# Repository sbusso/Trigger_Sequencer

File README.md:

# Trigger_Sequencer
4 channel 8 step trigger Eurorack sequencer with independent lenght and clock using an Arduino Nano.

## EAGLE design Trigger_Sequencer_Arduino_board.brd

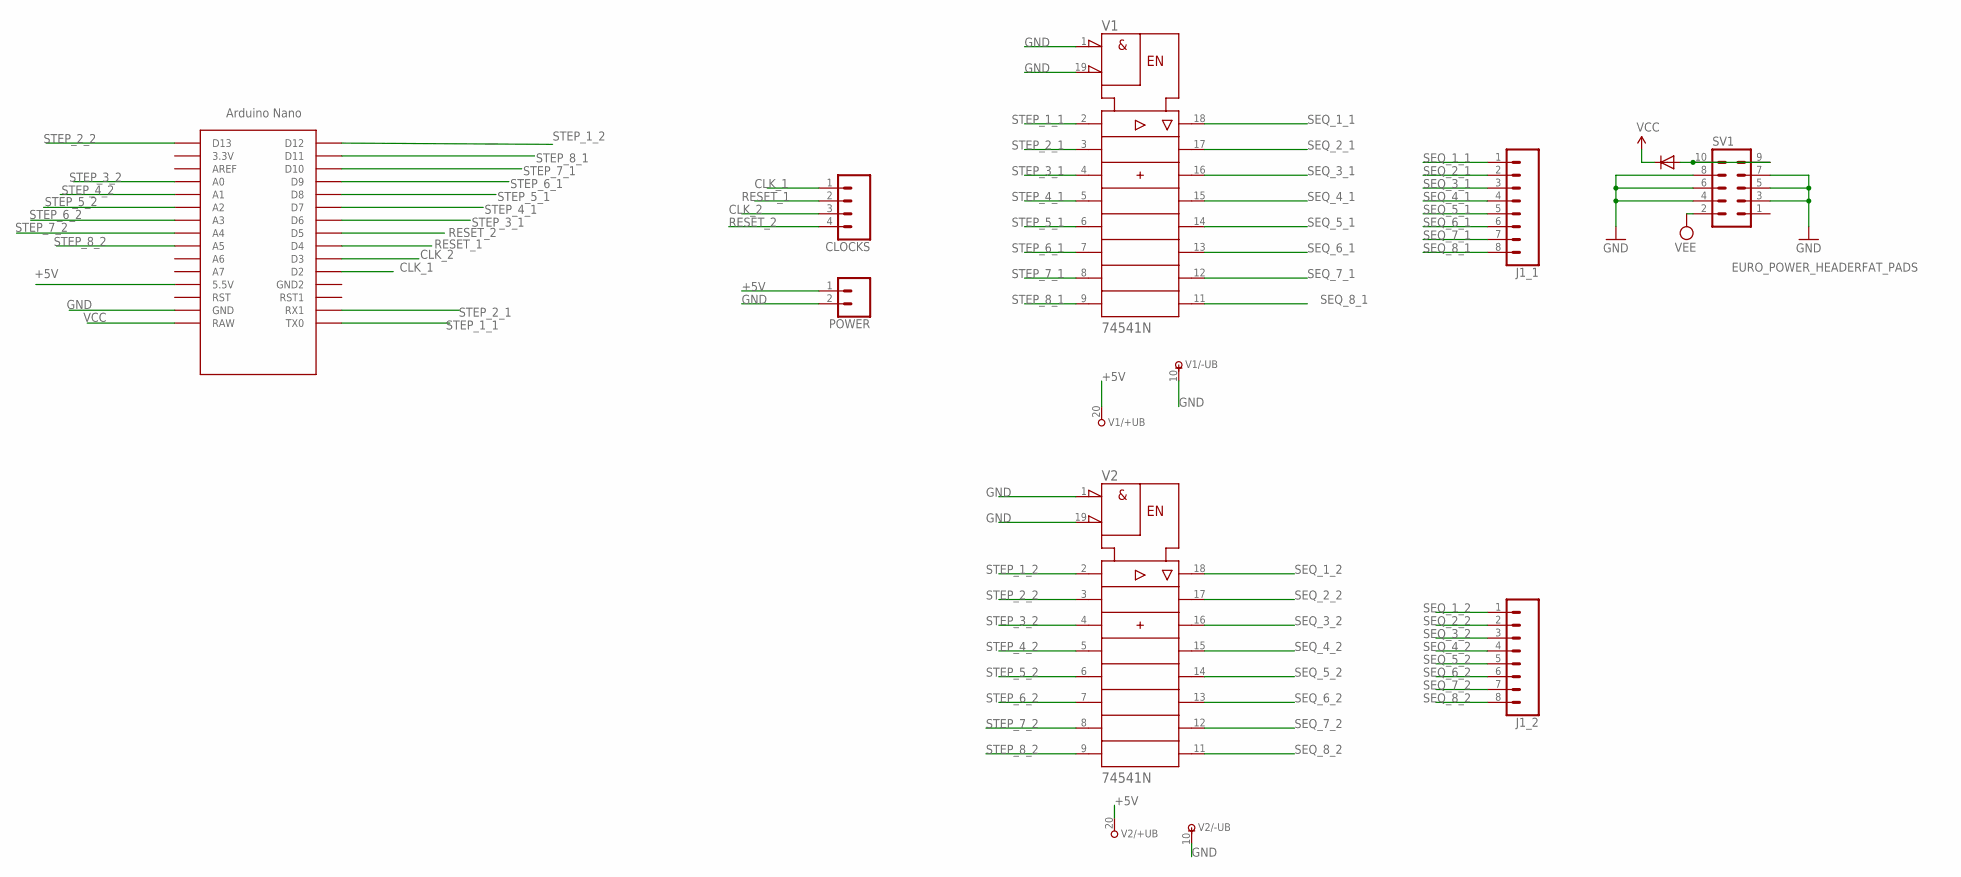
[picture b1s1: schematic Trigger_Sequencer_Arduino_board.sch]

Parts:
CLOCKS: CONN_04; 1X04
D2: 1N5819HW; DO-1N4148
J1_1, J1_2: CONN_08NO_SILK_FEMALE_PTH; 1X08_NO_SILK
POWER: CONN_02; 1X02
SV1: EURO_POWER_HEADERFAT_PADS; EURO_PWR_HEADER_FAT
U$1: NANO
V1, V2: 74541N; DIL20

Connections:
+5V: POWER.1, U$1.5V (5.5V), V1.20 (+UB), V2.20 (+UB)
CLK_1: CLOCKS.1, U$1.D2
CLK_2: CLOCKS.3, U$1.D3
GND: POWER.2, SV1.3, SV1.4, SV1.5, SV1.6, SV1.7, SV1.8, U$1.GND, V1.1 (!G1), V1.10 (-UB), V1.19 (!G2), V2.1 (!G1), V2.10 (-UB), V2.19 (!G2)
unnamed: D2.A, SV1.9, SV1.10
RESET_1: CLOCKS.2, U$1.D4
RESET_2: CLOCKS.4, U$1.D5
SEQ_1_1: J1_1.1, V1.18 (Y1)
SEQ_1_2: J1_2.1, V2.18 (Y1)
SEQ_2_1: J1_1.2, V1.17 (Y2)
SEQ_2_2: J1_2.2, V2.17 (Y2)
SEQ_3_1: J1_1.3, V1.16 (Y3)
SEQ_3_2: J1_2.3, V2.16 (Y3)
SEQ_4_1: J1_1.4, V1.15 (Y4)
SEQ_4_2: J1_2.4, V2.15 (Y4)
SEQ_5_1: J1_1.5, V1.14 (Y5)
SEQ_5_2: J1_2.5, V2.14 (Y5)
SEQ_6_1: J1_1.6, V1.13 (Y6)
SEQ_6_2: J1_2.6, V2.13 (Y6)
SEQ_7_1: J1_1.7, V1.12 (Y7)
SEQ_7_2: J1_2.7, V2.12 (Y7)
SEQ_8_1: J1_1.8, V1.11 (Y8)
SEQ_8_2: J1_2.8, V2.11 (Y8)
STEP_1_1: U$1.TX0, V1.2 (A1)
STEP_1_2: U$1.D12, V2.2 (A1)
STEP_2_1: U$1.RX1, V1.3 (A2)
STEP_2_2: U$1.D13, V2.3 (A2)
STEP_3_1: U$1.D6, V1.4 (A3)
STEP_3_2: U$1.A0, V2.4 (A3)
STEP_4_1: U$1.D7, V1.5 (A4)
STEP_4_2: U$1.A1, V2.5 (A4)
STEP_5_1: U$1.D8, V1.6 (A5)
STEP_5_2: U$1.A2, V2.6 (A5)
STEP_6_1: U$1.D9, V1.7 (A6)
STEP_6_2: U$1.A3, V2.7 (A6)
STEP_7_1: U$1.D10, V1.8 (A7)
STEP_7_2: U$1.A4, V2.8 (A7)
STEP_8_1: U$1.D11, V1.9 (A8)
STEP_8_2: U$1.A5, V2.9 (A8)
VCC: D2.C, U$1.RAW
VEE: SV1.2

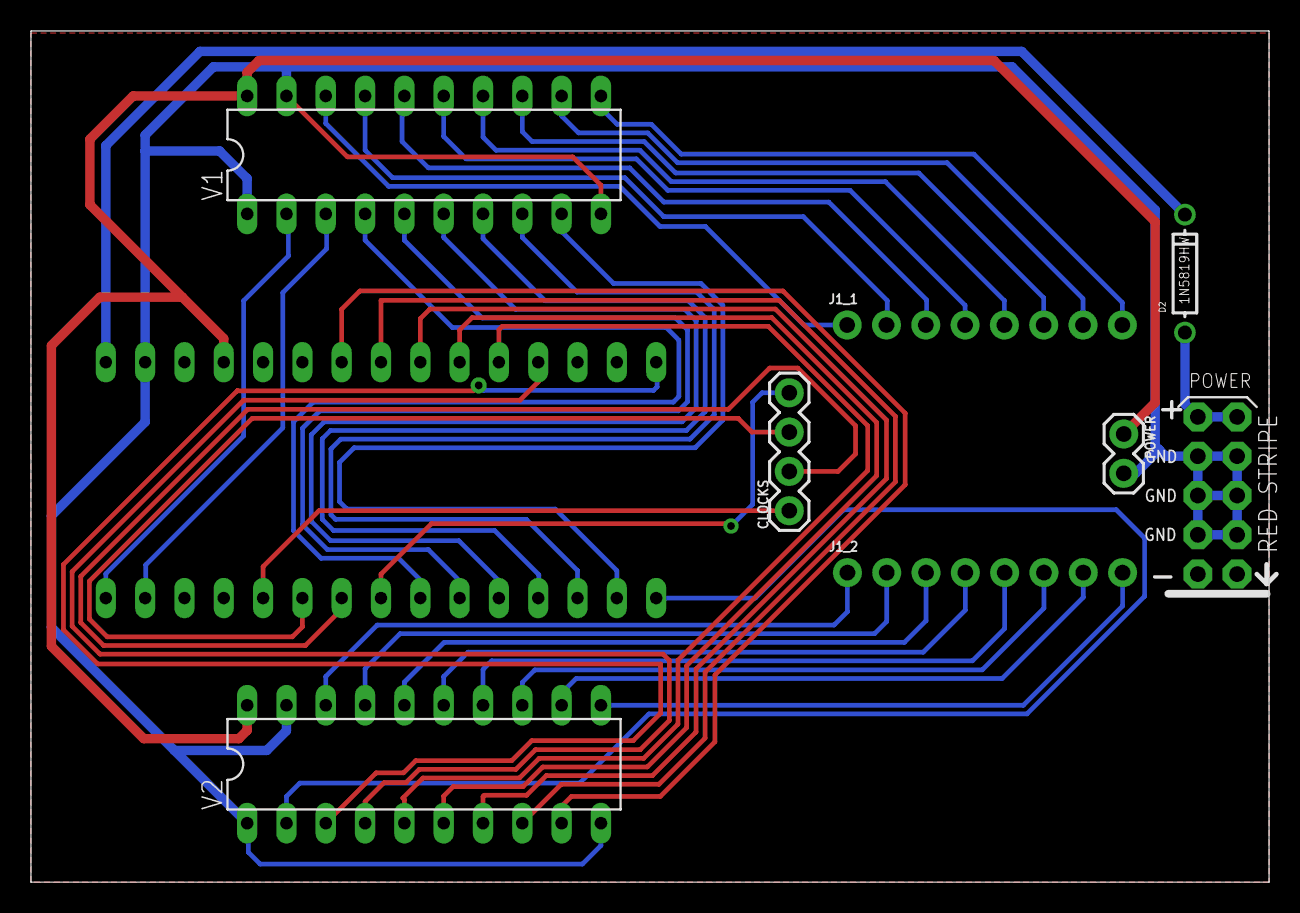
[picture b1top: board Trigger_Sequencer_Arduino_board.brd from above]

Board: 2 copper layers, 80.0 x 55.0 mm, 9 parts (0 on the bottom side), 40 nets.

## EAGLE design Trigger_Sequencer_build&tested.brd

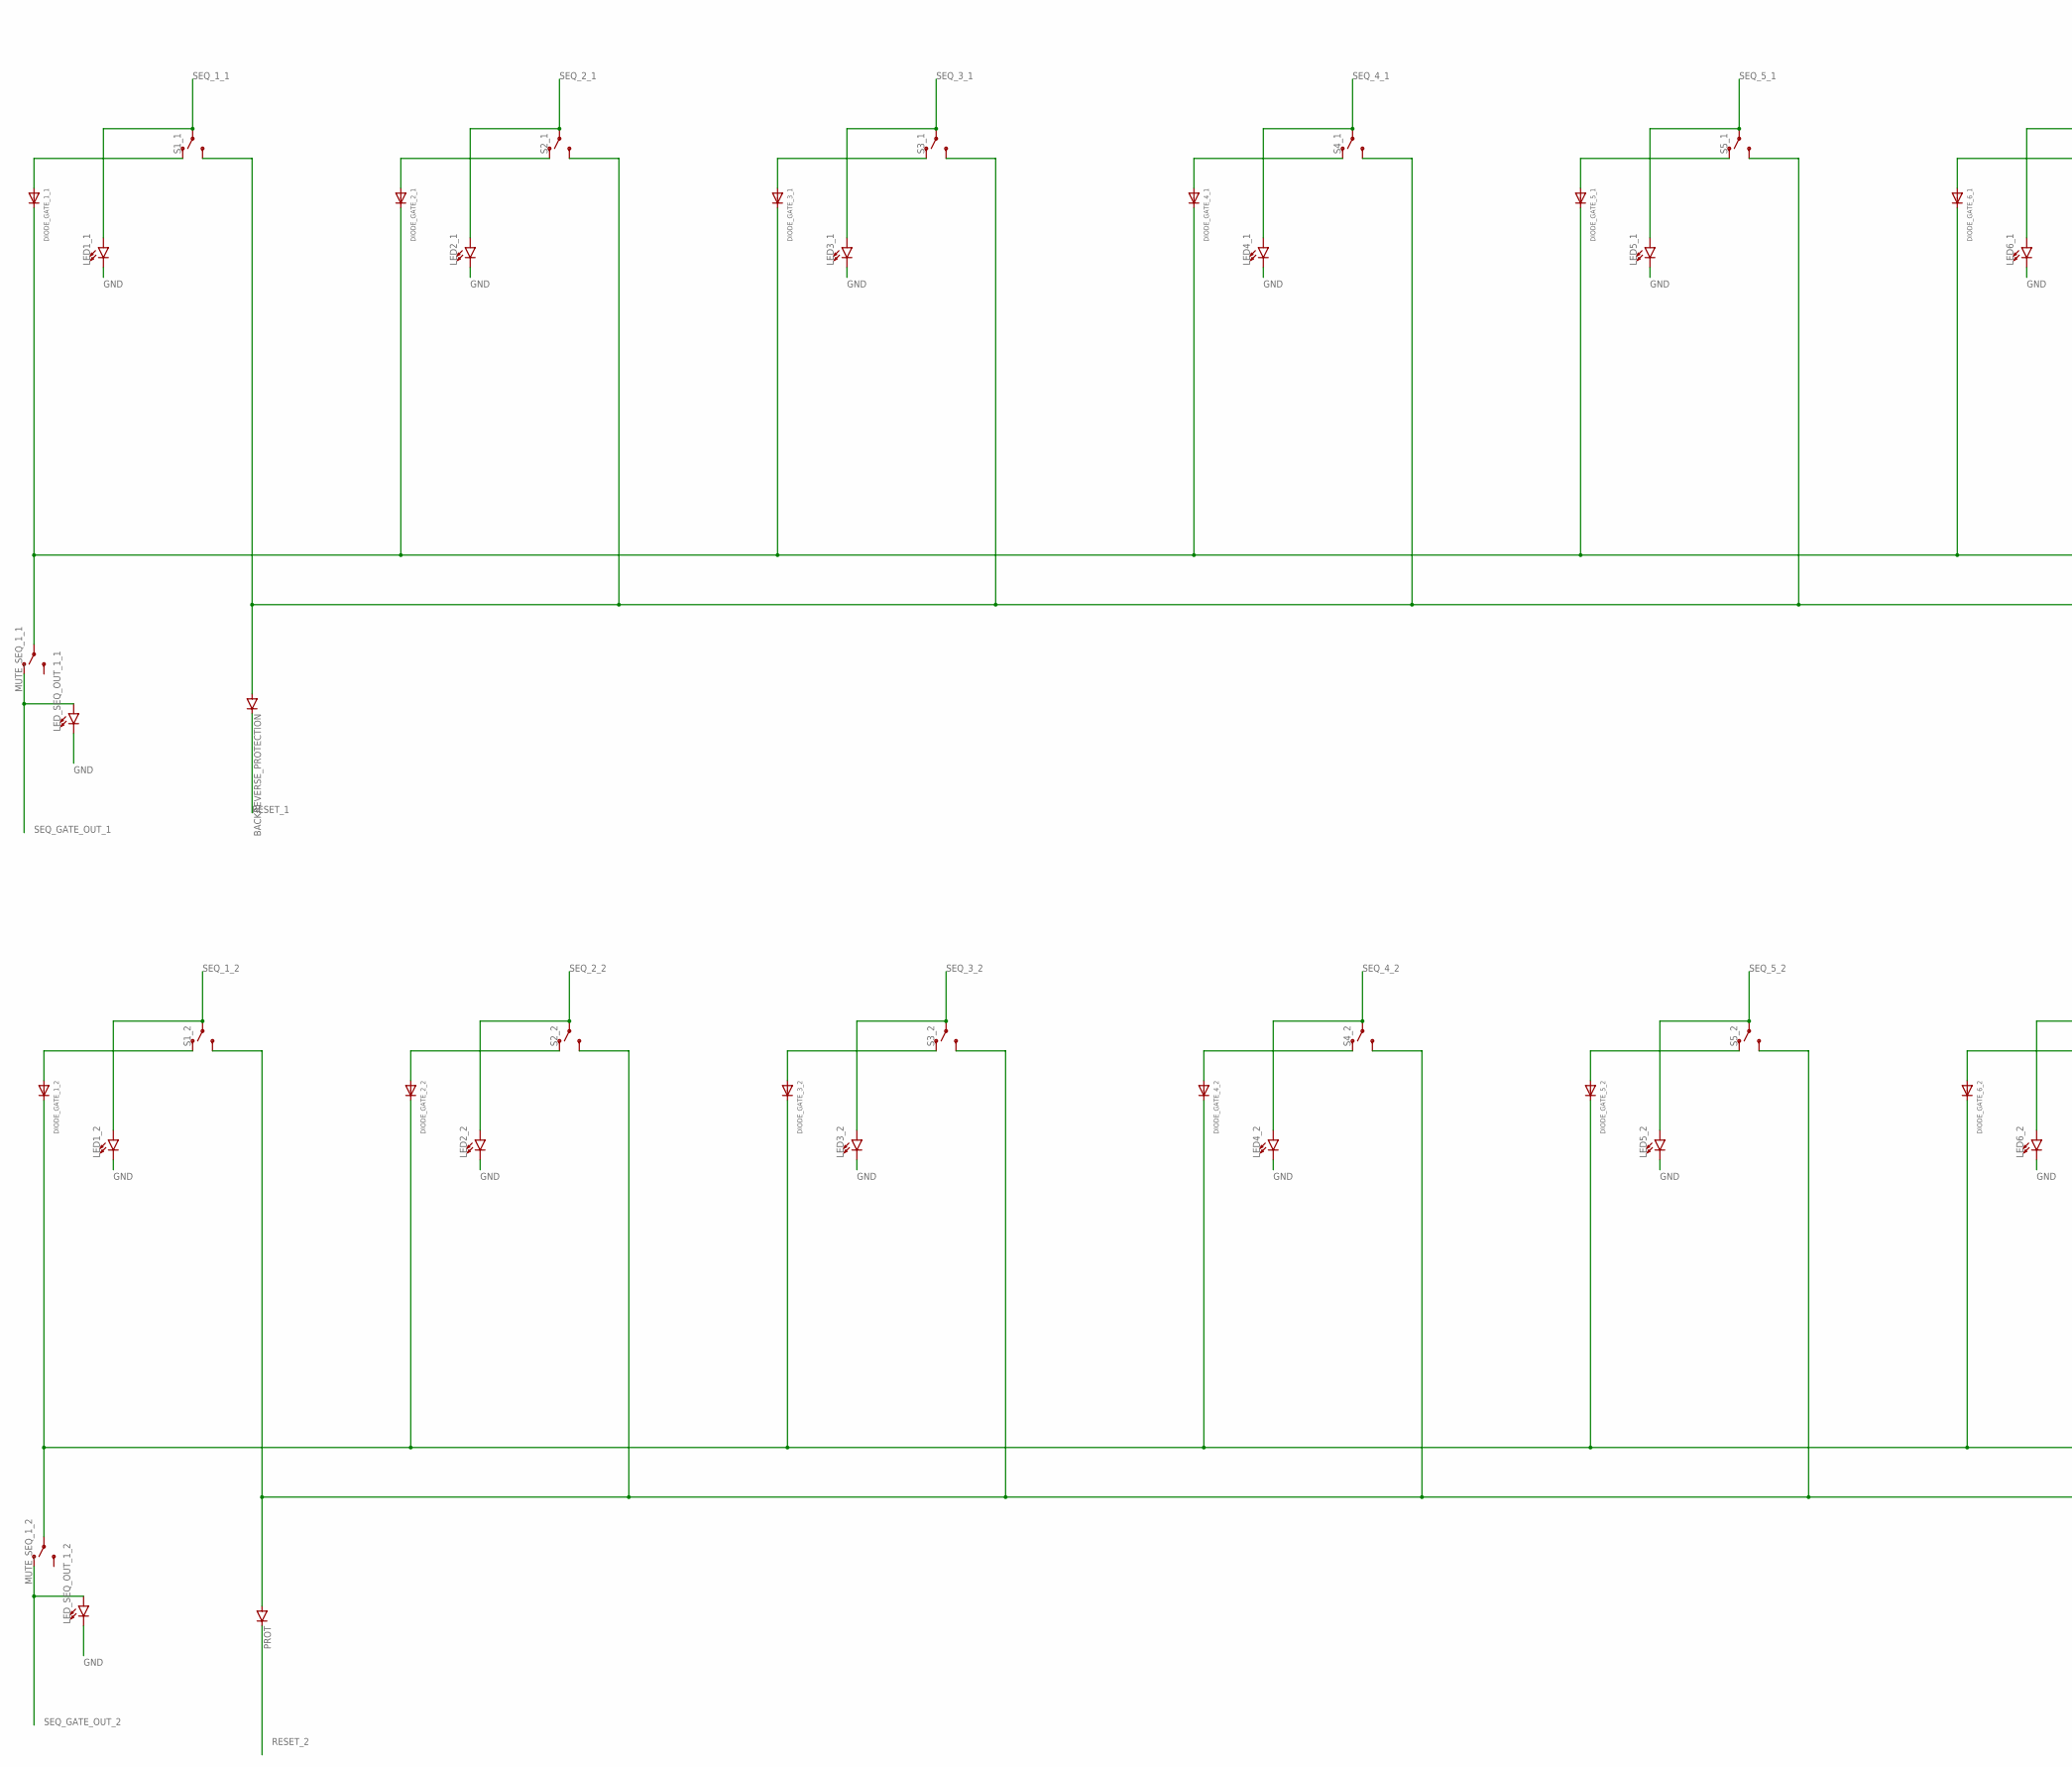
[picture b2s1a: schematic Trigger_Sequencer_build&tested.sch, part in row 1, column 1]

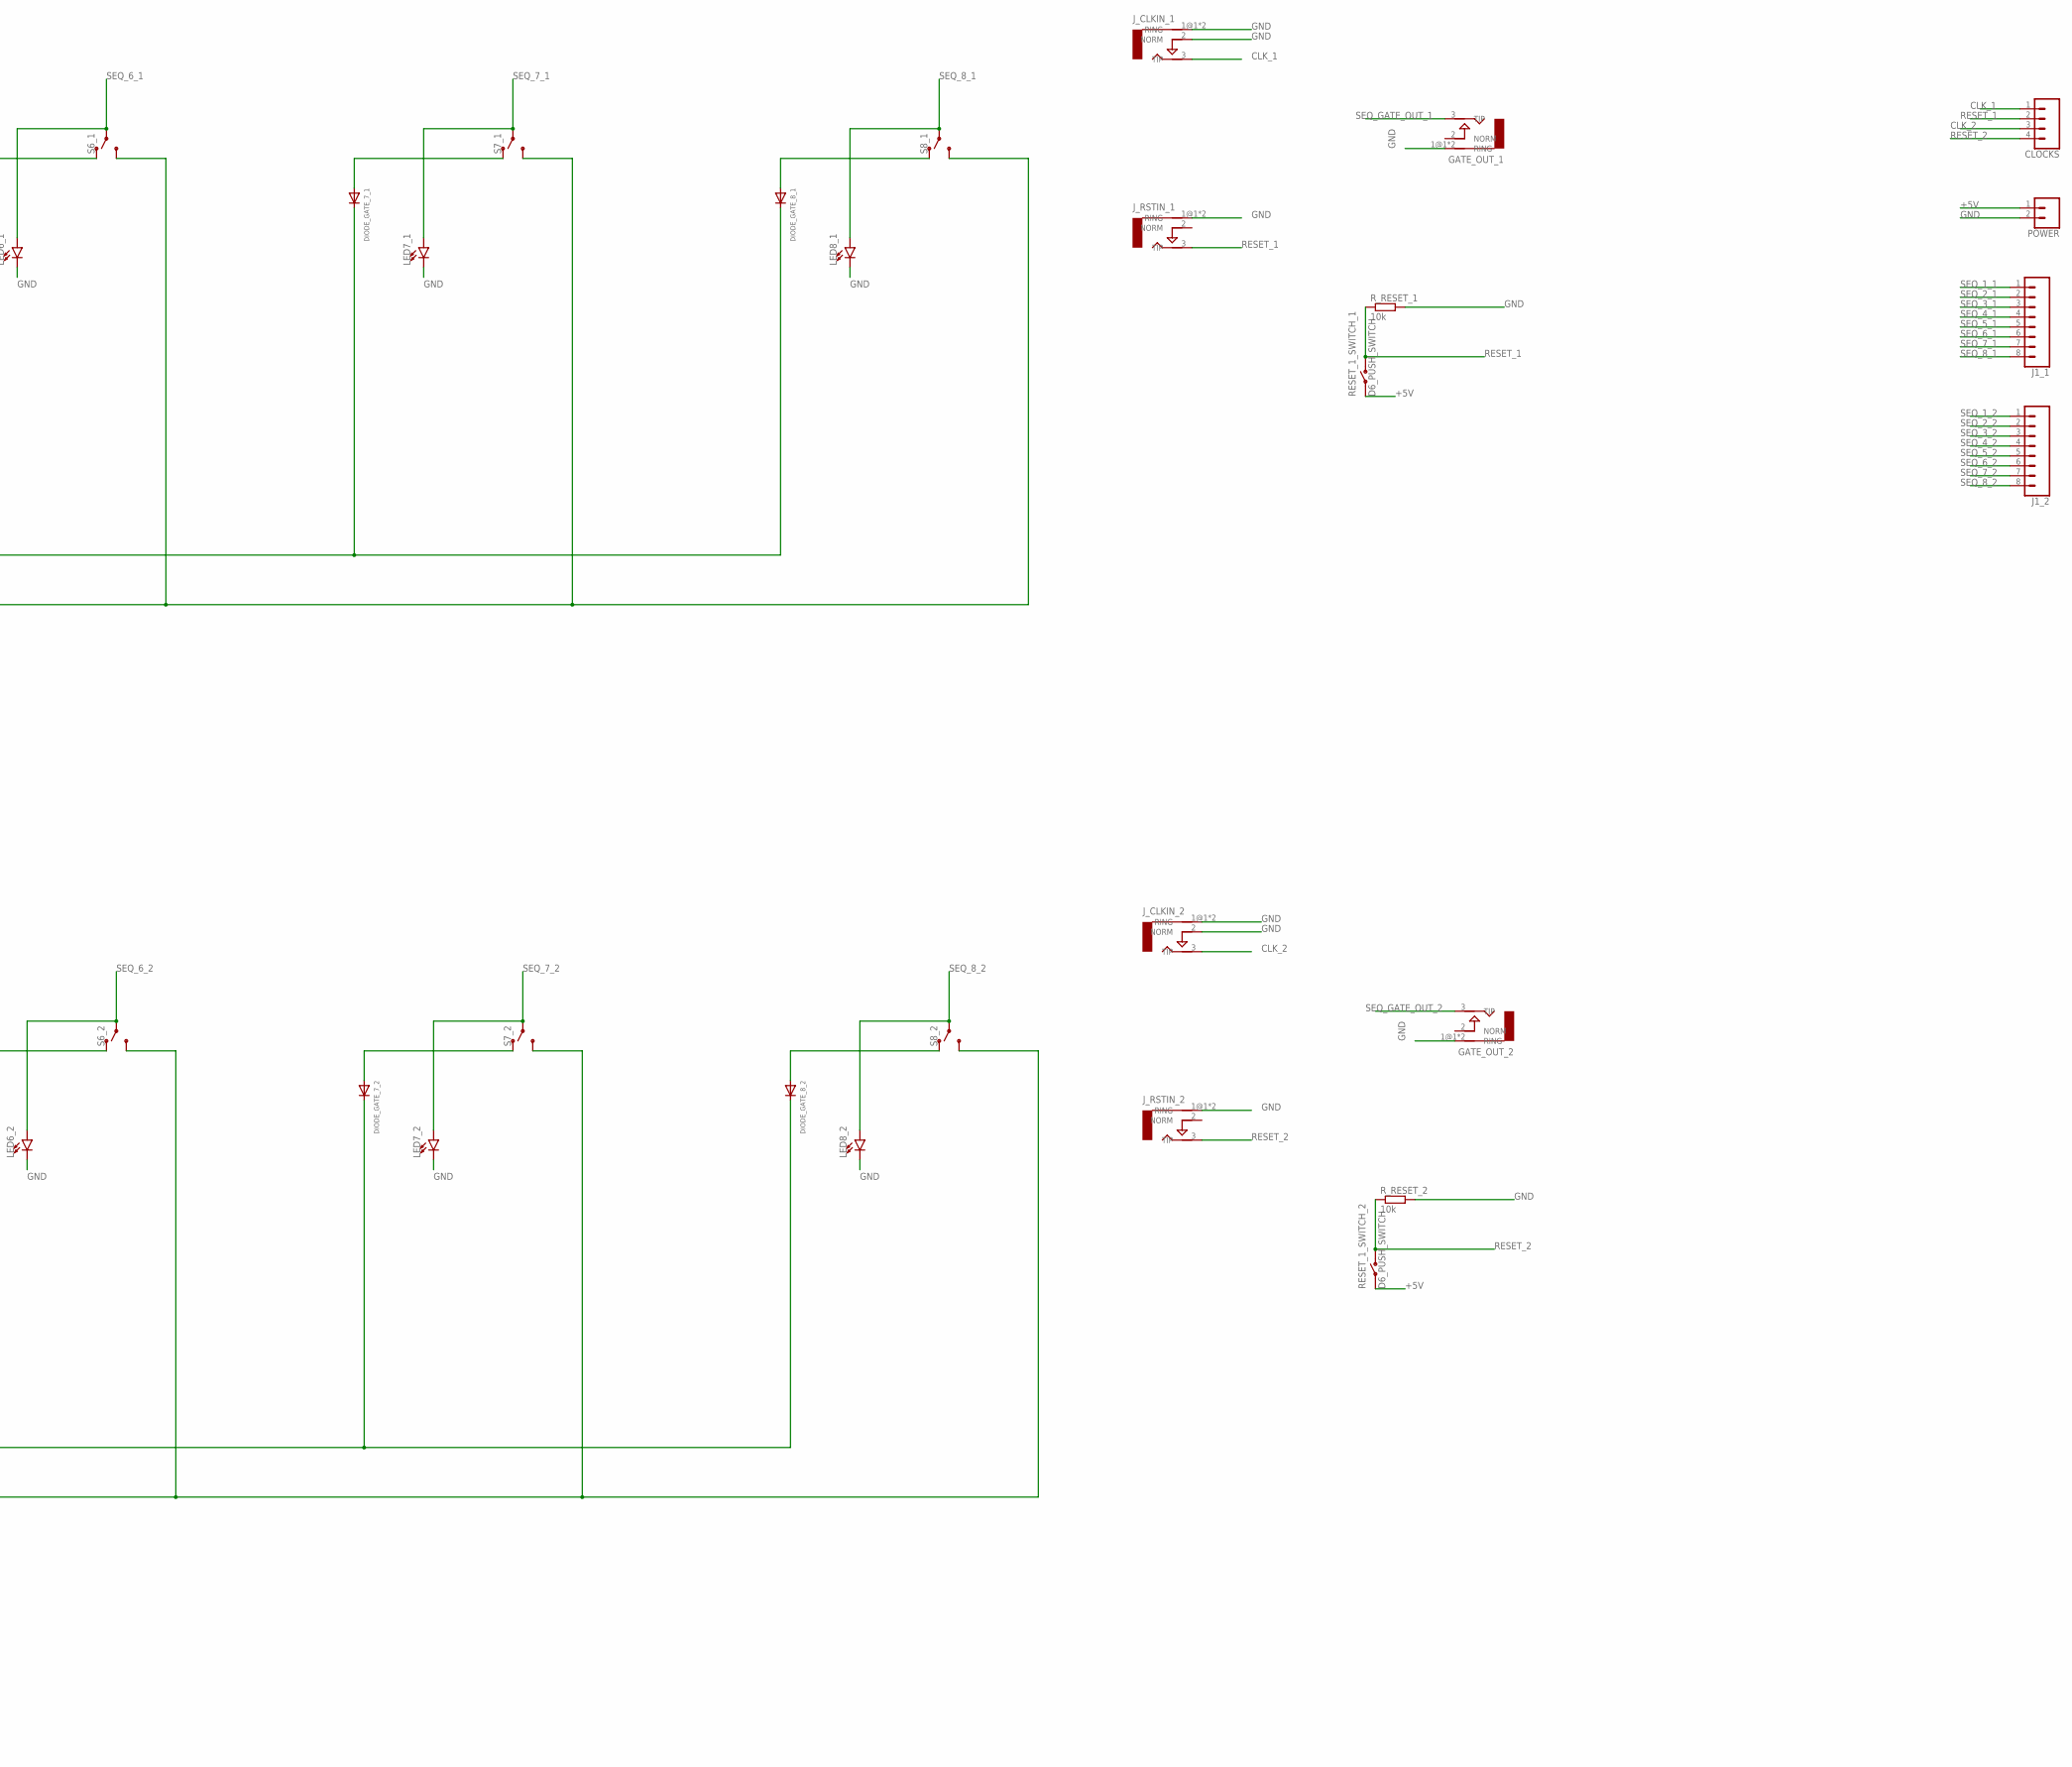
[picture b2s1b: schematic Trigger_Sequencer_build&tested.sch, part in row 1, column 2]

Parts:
BACKREVERSE_PROTECTION: DIODE1N4148; DIODE-1N4148
CLOCKS: CONN_04; 1X04
DIODE_GATE_1_1, DIODE_GATE_1_2, DIODE_GATE_2_1, DIODE_GATE_2_2, DIODE_GATE_3_1, DIODE_GATE_3_2, DIODE_GATE_4_1, DIODE_GATE_4_2, DIODE_GATE_5_1, DIODE_GATE_5_2, DIODE_GATE_6_1, DIODE_GATE_6_2, DIODE_GATE_7_1, DIODE_GATE_7_2, DIODE_GATE_8_1, DIODE_GATE_8_2: DIODEDO-1N4148; DO-1N4148
GATE_OUT_1, GATE_OUT_2: AUDIO-JACKERTHENVAR; ERTHENVAR-JACK
J1_1, J1_2: CONN_08NO_SILK_FEMALE_PTH; 1X08_NO_SILK
J_CLKIN_1, J_CLKIN_2: AUDIO-JACKERTHENVAR; ERTHENVAR-JACK
J_RSTIN_1, J_RSTIN_2: AUDIO-JACKERTHENVAR; ERTHENVAR-JACK
LED1_1, LED1_2, LED2_1, LED2_2, LED3_1, LED3_2, LED4_1, LED4_2, LED5_1, LED5_2, LED6_1, LED6_2, LED7_1, LED7_2, LED8_1, LED8_2: LED-3MM-NO_SILK; LED_3MM-NS
LED_SEQ_OUT_1_1, LED_SEQ_OUT_1_2: LED-3MM-NO_SILK; LED_3MM-NS
MUTE_SEQ_1_1, MUTE_SEQ_1_2: SWITCH-SPDT-PTH-11.6X4.0MM; SWITCH_SPDT_PTH_11.6X4.0MM
POWER: CONN_02; 1X02
PROT: DIODE1N4148; DIODE-1N4148
RESET_1_SWITCH_1, RESET_1_SWITCH_2: D6_PUSH_SWITCH
R_RESET_1, R_RESET_2: 10k; VERTICAL_RESISTOR
S1_1, S1_2, S2_1, S2_2, S3_1, S3_2, S4_1, S4_2, S5_1, S5_2, S6_1, S6_2, S7_1, S7_2, S8_1, S8_2: SWITCH-SPDT-PTH-11.6X4.0MM; SWITCH_SPDT_PTH_11.6X4.0MM

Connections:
+5V: POWER.1, RESET_1_SWITCH_1.P$3, RESET_1_SWITCH_1.P$4, RESET_1_SWITCH_2.P$3, RESET_1_SWITCH_2.P$4
CLK_1: CLOCKS.1, J_CLKIN_1.3 (TIP)
CLK_2: CLOCKS.3, J_CLKIN_2.3 (TIP)
GND: GATE_OUT_1.1@1 (RING), GATE_OUT_1.1@2 (RING), GATE_OUT_2.1@1 (RING), GATE_OUT_2.1@2 (RING), J_CLKIN_1.1@1 (RING), J_CLKIN_1.1@2 (RING), J_CLKIN_1.2 (NORM), J_CLKIN_2.1@1 (RING), J_CLKIN_2.1@2 (RING), J_CLKIN_2.2 (NORM), J_RSTIN_1.1@1 (RING), J_RSTIN_1.1@2 (RING), J_RSTIN_2.1@1 (RING), J_RSTIN_2.1@2 (RING), LED1_1.K (C), LED1_2.K (C), LED2_1.K (C), LED2_2.K (C), LED3_1.K (C), LED3_2.K (C), LED4_1.K (C), LED4_2.K (C), LED5_1.K (C), LED5_2.K (C), LED6_1.K (C), LED6_2.K (C), LED7_1.K (C), LED7_2.K (C), LED8_1.K (C), LED8_2.K (C), LED_SEQ_OUT_1_1.K (C), LED_SEQ_OUT_1_2.K (C), POWER.2, R_RESET_1.2, R_RESET_2.2
unnamed: DIODE_GATE_1_2.A, S1_2.1 (O)
unnamed: DIODE_GATE_1_1.A, S1_1.1 (O)
unnamed: DIODE_GATE_2_2.A, S2_2.1 (O)
unnamed: DIODE_GATE_3_2.A, S3_2.1 (O)
unnamed: DIODE_GATE_4_2.A, S4_2.1 (O)
unnamed: DIODE_GATE_2_1.A, S2_1.1 (O)
unnamed: DIODE_GATE_5_2.A, S5_2.1 (O)
unnamed: DIODE_GATE_6_2.A, S6_2.1 (O)
unnamed: DIODE_GATE_7_2.A, S7_2.1 (O)
unnamed: DIODE_GATE_3_1.A, S3_1.1 (O)
unnamed: DIODE_GATE_8_2.A, S8_2.1 (O)
unnamed: DIODE_GATE_4_1.A, S4_1.1 (O)
unnamed: DIODE_GATE_5_1.A, S5_1.1 (O)
unnamed: DIODE_GATE_6_1.A, S6_1.1 (O)
unnamed: DIODE_GATE_7_1.A, S7_1.1 (O)
unnamed: DIODE_GATE_8_1.A, S8_1.1 (O)
RESET_1: BACKREVERSE_PROTECTION.A, BACKREVERSE_PROTECTION.C, CLOCKS.2, J_RSTIN_1.3 (TIP), RESET_1_SWITCH_1.P$1 (O), RESET_1_SWITCH_1.P$2 (O), R_RESET_1.1, S1_1.3 (S), S2_1.3 (S), S3_1.3 (S), S4_1.3 (S), S5_1.3 (S), S6_1.3 (S), S7_1.3 (S), S8_1.3 (S)
RESET_2: CLOCKS.4, J_RSTIN_2.3 (TIP), PROT.A, PROT.C, RESET_1_SWITCH_2.P$1 (O), RESET_1_SWITCH_2.P$2 (O), R_RESET_2.1, S1_2.3 (S), S2_2.3 (S), S3_2.3 (S), S4_2.3 (S), S5_2.3 (S), S6_2.3 (S), S7_2.3 (S), S8_2.3 (S)
SEQ_1_1: J1_1.1, LED1_1.A, S1_1.2
SEQ_1_2: J1_2.1, LED1_2.A, S1_2.2
SEQ_2_1: J1_1.2, LED2_1.A, S2_1.2
SEQ_2_2: J1_2.2, LED2_2.A, S2_2.2
SEQ_3_1: J1_1.3, LED3_1.A, S3_1.2
SEQ_3_2: J1_2.3, LED3_2.A, S3_2.2
SEQ_4_1: J1_1.4, LED4_1.A, S4_1.2
SEQ_4_2: J1_2.4, LED4_2.A, S4_2.2
SEQ_5_1: J1_1.5, LED5_1.A, S5_1.2
SEQ_5_2: J1_2.5, LED5_2.A, S5_2.2
SEQ_6_1: J1_1.6, LED6_1.A, S6_1.2
SEQ_6_2: J1_2.6, LED6_2.A, S6_2.2
SEQ_7_1: J1_1.7, LED7_1.A, S7_1.2
SEQ_7_2: J1_2.7, LED7_2.A, S7_2.2
SEQ_8_1: J1_1.8, LED8_1.A, S8_1.2
SEQ_8_2: J1_2.8, LED8_2.A, S8_2.2
SEQ_GATE_OUT_1: GATE_OUT_1.3 (TIP), LED_SEQ_OUT_1_1.A, MUTE_SEQ_1_1.1 (O)
SEQ_GATE_OUT_2: GATE_OUT_2.3 (TIP), LED_SEQ_OUT_1_2.A, MUTE_SEQ_1_2.1 (O)
TO_GATE_BUS: DIODE_GATE_1_1.C, DIODE_GATE_2_1.C, DIODE_GATE_3_1.C, DIODE_GATE_4_1.C, DIODE_GATE_5_1.C, DIODE_GATE_6_1.C, DIODE_GATE_7_1.C, DIODE_GATE_8_1.C, MUTE_SEQ_1_1.2
TO_GATE_BUS1: DIODE_GATE_1_2.C, DIODE_GATE_2_2.C, DIODE_GATE_3_2.C, DIODE_GATE_4_2.C, DIODE_GATE_5_2.C, DIODE_GATE_6_2.C, DIODE_GATE_7_2.C, DIODE_GATE_8_2.C, MUTE_SEQ_1_2.2

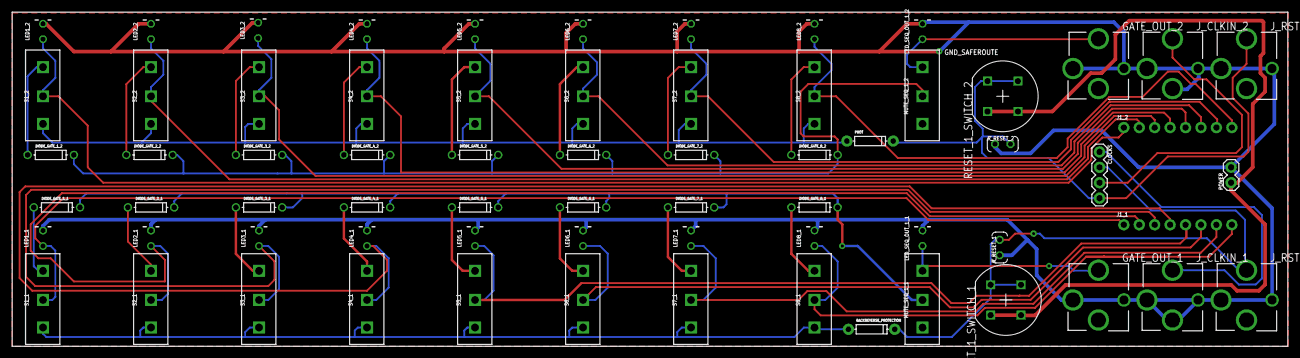
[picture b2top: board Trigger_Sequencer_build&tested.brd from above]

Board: 2 copper layers, 210.0 x 55.0 mm, 68 parts (0 on the bottom side), 42 nets.

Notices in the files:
parts and their libraries:
SparkFun-Connectors: Licensing: Creative Commons ShareAlike 4.0 International - https://creativecommons.org/licenses/by-sa/4.0
